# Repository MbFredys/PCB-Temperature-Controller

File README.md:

# Temperature Controller — Hardware Design

Temperature-control PCB design integrating sensing, local displays, setpoint buttons and a relay output.

> **Status: hardware design requiring review and prototype validation.** KiCad sources, a PDF schematic, PCB renders and fabrication exports are published. Firmware is not provided. Temperature accuracy, control stability, Bluetooth operation and electrical safety are not demonstrated by the repository.

## Intended architecture

The published component netlist includes:

- **ATmega328P-AU** microcontroller.
- **MAX31855TASA** thermocouple interface.
- **AD623** instrumentation amplifier in the PT100-related circuit.
- **BTM112** Bluetooth module.
- Two **CA56-12EWA** display assemblies with shift-register/multiplexing circuitry.
- **FINDER 36.11** relay and transistor driver.
- **RAC01-05SGB** AC/DC module and **LM1117-3.3** regulator.

PT100 and thermocouple inputs are design intentions. Supported sensor ranges, excitation, calibration, error budget and fault detection must be established from a complete circuit review and measurements.

## Engineering scope

The project brings together analog sensing, digital display interfacing, a user interface, communication hardware and load control. The available files document the proposed circuit and PCB, rather than a validated controller.

## Required verification

- Confirm module variants, pin assignments, voltage levels and the complete power budget.
- Review the PT100 excitation and amplifier gain, offset, input range and error budget.
- Check thermocouple type, cold-junction behavior and fault response.
- Verify display drive currents and multiplexing timing.
- Define sensor-fault handling, relay safe state, hysteresis/control law and watchdog behavior.
- Review mains separation, creepage/clearance, fusing, enclosure and relay/load ratings before any powered work.
- Develop firmware and record prototype tests.

The AC input range of a selected module does not establish the safety or certification of the complete PCB. Existing Gerbers must not be treated as a fabrication release.

## Files

- [KiCAD files](KiCAD%20files/): editable sources and exported component/net information.
- [PDF schematic](PDF%20Schematic/Controlador-temperatura.pdf).
- [Manufacturing](Manufacturing/): historical fabrication outputs.
- [Release](Release/): PCB renders.
- [Firmware](Firmware/): availability note.

The legacy project uses the `.sch` / `.pro` file format. Preserve an original copy and verify any migration in a supported KiCad version.

## Contributing

Proposed improvements should state the circuit change, its rationale and the checks performed. Keep schematic, PCB, BOM and fabrication outputs synchronized.

## License

CERN-OHL-W-2.0. See [LICENSE](LICENSE) and [COPYING](COPYING).

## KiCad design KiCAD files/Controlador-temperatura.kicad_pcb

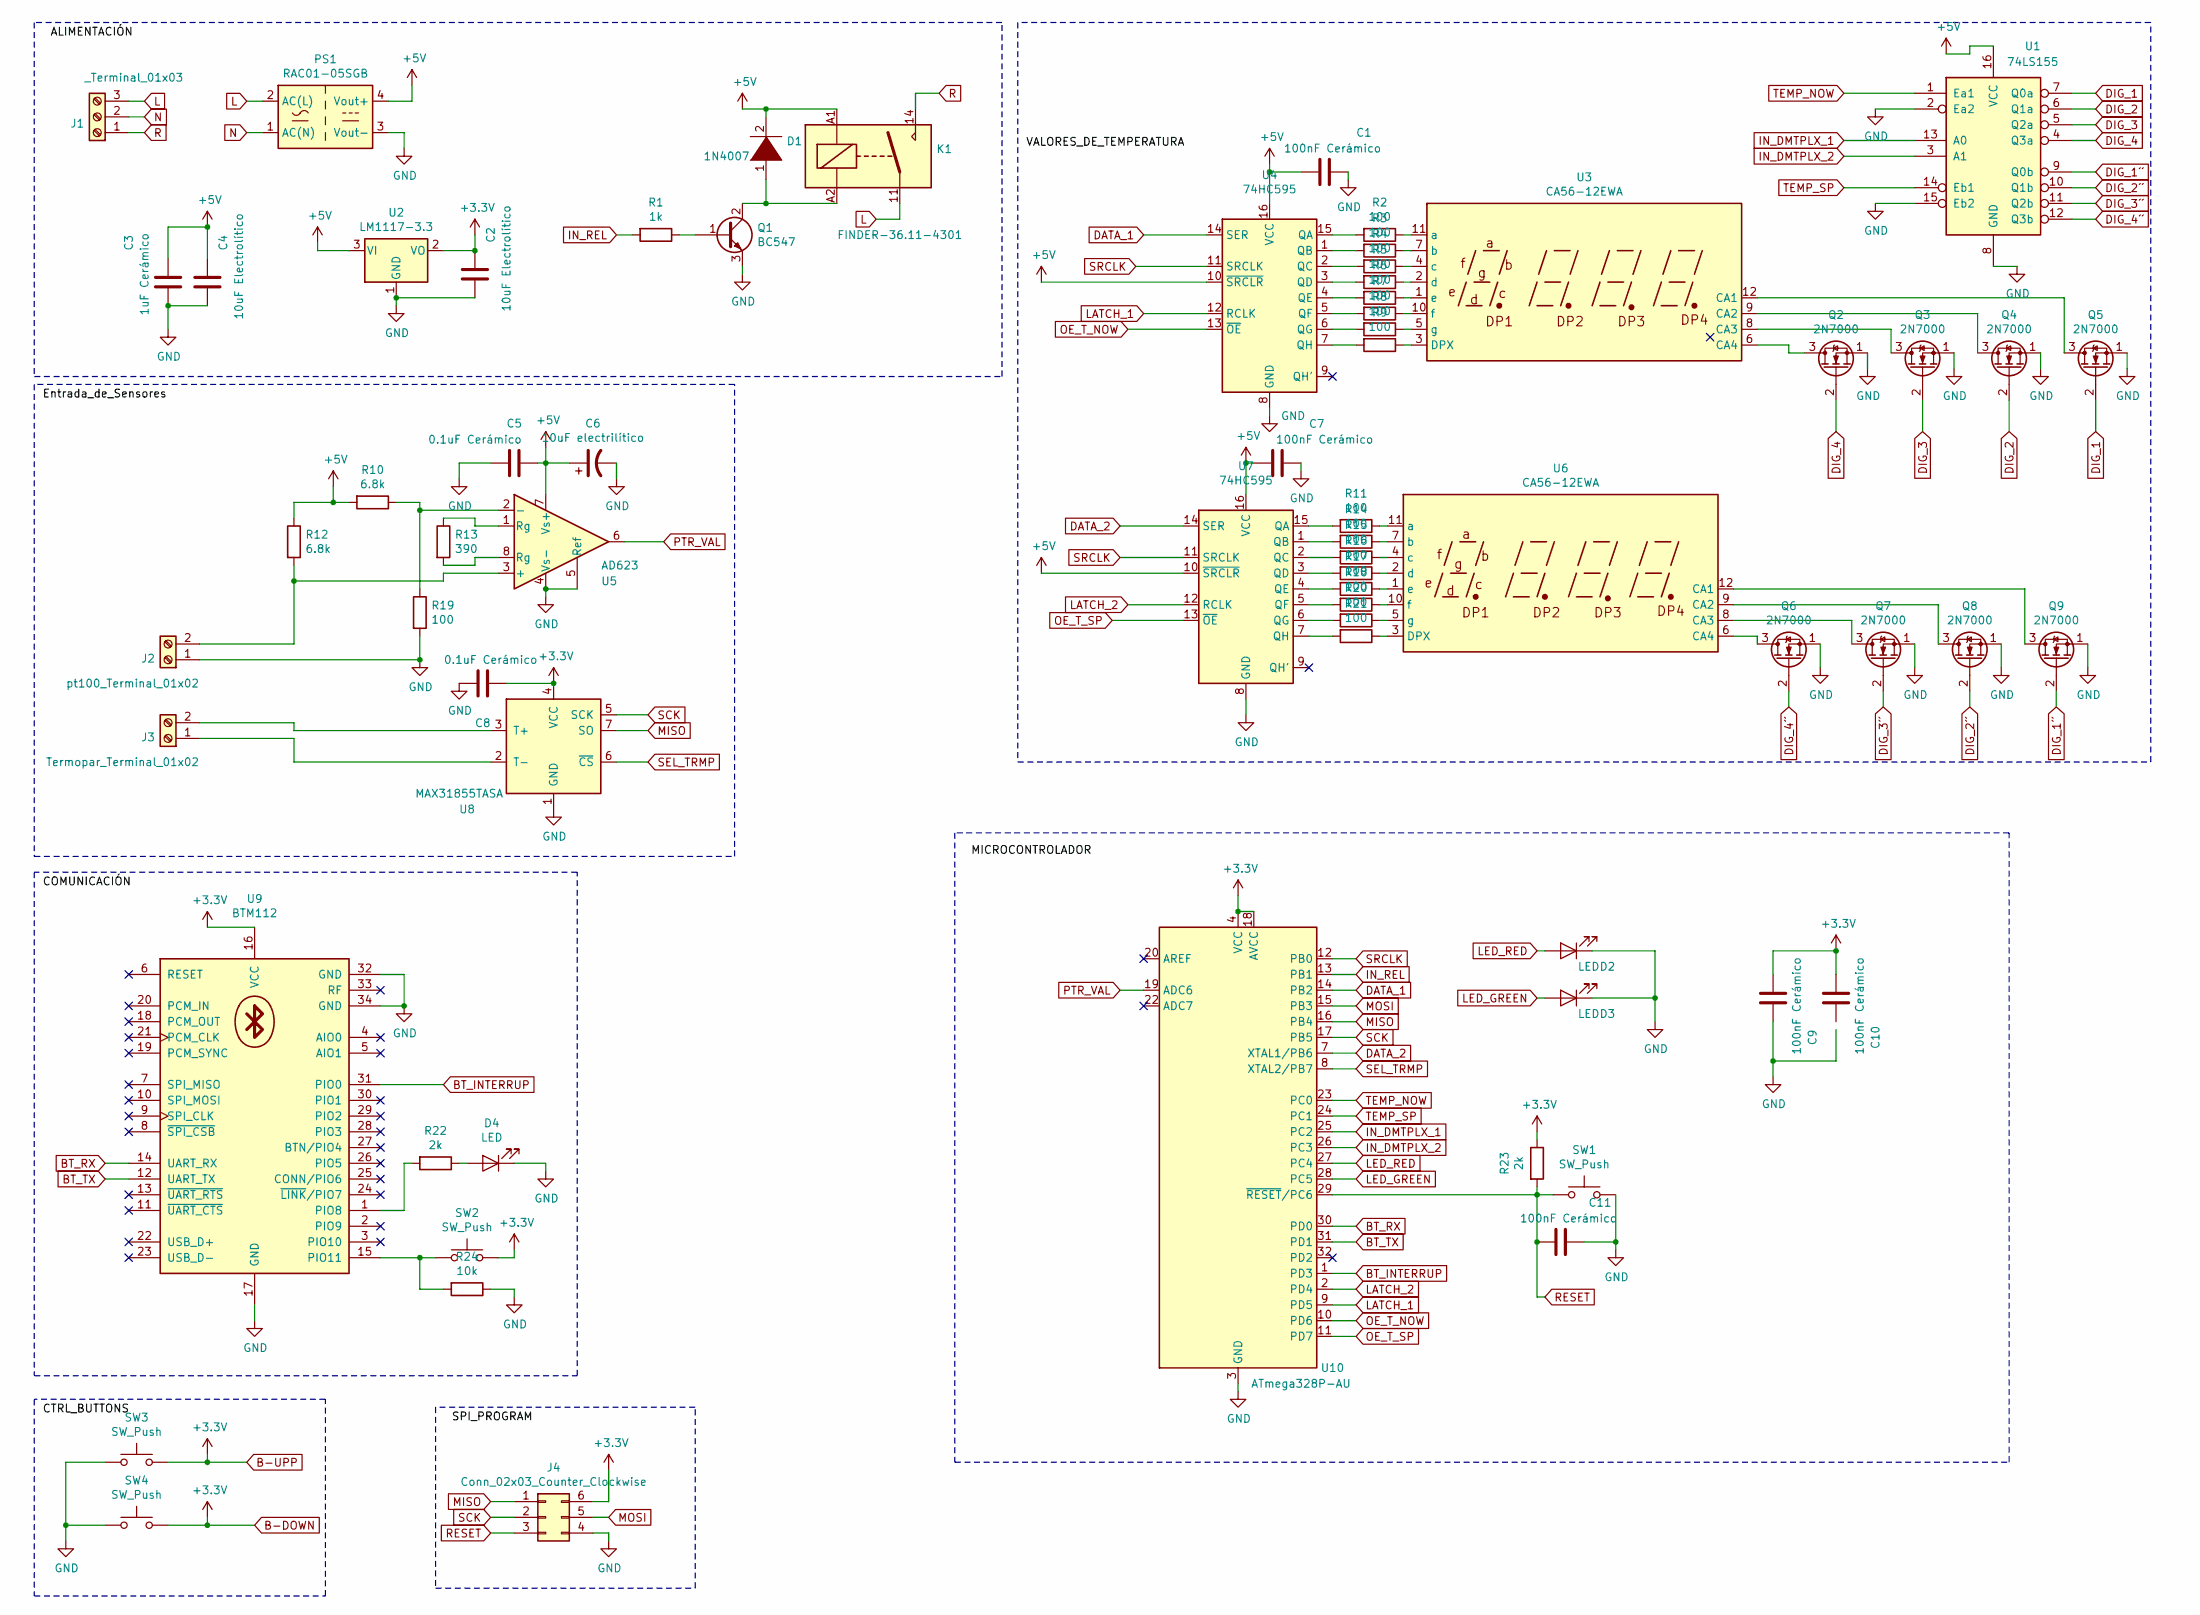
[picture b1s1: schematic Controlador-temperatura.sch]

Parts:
C1, C7, C9, C10, C11: 100nF Cerámico; C_1812_4532Metric_Pad1.30x3.40mm_HandSolder
C2, C4: 10uF Electrolítico; CP_Elec_4x4.5
C3: 1uF Cerámico; C_2512_6332Metric_Pad1.52x3.35mm_HandSolder
C5: 0.1uF Cerámico; C_2512_6332Metric_Pad1.52x3.35mm_HandSolder
C6: 10uF electrilítico; CP_Elec_4x4.5
C8: 0.1uF Cerámico; CP_Elec_4x4.5
D1: 1N4007; D_SOD-323
D2: LED; LED_D3.0mm_IRBlack
D3: LED; LED_D3.0mm_IRGrey
D4: LED; LED_1206_3216Metric
J1: _Terminal_01x03; TerminalBlock_Altech_AK300-3_P5.00mm
J2: pt100_Terminal_01x02; Altech_AK300_1x02_P5.00mm_45-Degree
J3: Termopar_Terminal_01x02; Altech_AK300_1x02_P5.00mm_45-Degree
J4: Conn_02x03_Counter_Clockwise; PinHeader_2x03_P1.27mm_Vertical
K1: FINDER-36.11-4301; Relay_SPST_Finder_32.21-x300
PS1: RAC01-05SGB; Converter_ACDC_RECOM_RAC01-xxSGB_THT
Q1: BC547; SC-59
Q2, Q3, Q4, Q5, Q6, Q7, Q8, Q9: 2N7000; SC-59
R1: 1k; R_0805_2012Metric_Pad1.15x1.40mm_HandSolder
R2, R3, R4, R5, R6, R7, R8, R9, R11, R14, R15, R16, R17, R18, R19, R20, R21: 100; R_0603_1608Metric
R10, R12: 6.8k; R_0805_2012Metric_Pad1.15x1.40mm_HandSolder
R13: 390; R_0603_1608Metric
R22, R23: 2k; R_0805_2012Metric_Pad1.15x1.40mm_HandSolder
R24: 10k; R_0805_2012Metric_Pad1.15x1.40mm_HandSolder
SW1, SW2, SW3, SW4: SW_Push; SW_SPST_B3U-1000P
U1: 74LS155; SOIC-16_3.9x9.9mm_P1.27mm
U2: LM1117-3.3; SOT-223-3_TabPin2
U3, U6: CA56-12EWA
U4, U7: 74HC595; SOIC-16_3.9x9.9mm_P1.27mm
U5: AD623; PowerIntegrations_SO-8
U8: MAX31855TASA; SOIC-8_3.9x4.9mm_P1.27mm
U9: BTM112; BTM-112
U10: ATmega328P-AU; TQFP-32_7x7mm_P0.8mm

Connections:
+5V: C1.1, C3.2, C4.2, C5.1, C6.1, C7.1, D1.2 (A), K1.A1, PS1.4 (Vout+), R10.2, R12.1, U1.16 (VCC), U2.3 (VI), U4.10 (~SRCLR), U4.16 (VCC), U5.7 (Vs+), U7.10 (~SRCLR), U7.16 (VCC)
B-DOWN: C2.2, C8.2, C9.1, C10.1, J4.6, R23.1, SW2.2, SW3.2, SW4.2, U2.2 (VO), U8.4 (VCC), U9.16 (VCC), U10.4 (VCC), U10.6 (VCC), U10.18 (AVCC)
BT_INTERRUP: U9.31 (PIO0), U10.1 (PD3)
BT_RX: U9.14 (UART_RX), U10.30 (PD0)
BT_TX: U9.12 (UART_TX), U10.31 (PD1)
DATA_1: U4.14 (SER), U10.14 (PB2)
DATA_2: U7.14 (SER), U10.7 (XTAL1/PB6)
DIG_1: Q5.2 (G), U1.7 (Q0a)
DIG_1´´: Q9.2 (G), U1.9 (Q0b)
DIG_2: Q4.2 (G), U1.6 (Q1a)
DIG_2´´: Q8.2 (G), U1.10 (Q1b)
DIG_3: Q3.2 (G), U1.5 (Q2a)
DIG_3´´: Q7.2 (G), U1.11 (Q2b)
DIG_4: Q2.2 (G), U1.4 (Q3a)
DIG_4´´: Q6.2 (G), U1.12 (Q3b)
GND: C1.2, C2.1, C3.1, C4.1, C5.2, C6.2, C7.2, C8.1, C9.2, C11.2, D2.1 (K), D3.1 (K), D4.1 (K), J2.1, J4.4, PS1.3 (Vout-), Q1.3 (E), Q2.1 (S), Q3.1 (S), Q4.1 (S), Q5.1 (S), Q6.1 (S), Q7.1 (S), Q8.1 (S), Q9.1 (S), R19.2, R24.1, SW1.2, SW3.1, SW4.1, U1.2 (Ea2), U1.8 (GND), U1.15 (Eb2), U2.1 (GND), U4.8 (GND), U5.4 (Vs-), U5.5 (Ref), U7.8 (GND), U8.1 (GND), U9.17 (GND), U9.32 (GND), U9.34 (GND), U10.3 (GND), U10.5 (GND), U10.21 (GND)
IN_DMTPLX_1: U1.13 (A0), U10.25 (PC2)
IN_DMTPLX_2: U1.3 (A1), U10.26 (PC3)
IN_REL: R1.2, U10.13 (PB1)
L: J1.3, K1.11, PS1.2 (AC(L))
LATCH_1: U4.12 (RCLK), U10.9 (PD5)
LATCH_2: U7.12 (RCLK), U10.2 (PD4)
LED_GREEN: D3.2 (A), U10.28 (PC5)
LED_RED: D2.2 (A), U10.27 (PC4)
MISO: J4.1, U8.7 (SO), U10.16 (PB4)
MOSI: J4.5, U10.15 (PB3)
N: J1.2, PS1.1 (AC(N))
unnamed: D1.1 (K), K1.A2, Q1.2 (C)
unnamed: D4.2 (A), R22.1
unnamed: J2.2, R12.2, U5.3 (+)
unnamed: J3.1, U8.2 (T-)
unnamed: J3.2, U8.3 (T+)
unnamed: Q1.1 (B), R1.1
unnamed: Q2.3 (D), U3.6 (CA4)
unnamed: Q3.3 (D), U3.8 (CA3)
unnamed: Q4.3 (D), U3.9 (CA2)
unnamed: Q5.3 (D), U3.12 (CA1)
unnamed: Q6.3 (D), U6.6 (CA4)
unnamed: Q7.3 (D), U6.8 (CA3)
unnamed: Q8.3 (D), U6.9 (CA2)
unnamed: Q9.3 (D), U6.12 (CA1)
unnamed: R2.1, U3.11 (a)
unnamed: R2.2, U4.15 (QA)
unnamed: R3.1, U3.7 (b)
unnamed: R3.2, U4.1 (QB)
unnamed: R4.1, U3.4 (c)
unnamed: R4.2, U4.2 (QC)
unnamed: R5.1, U3.2 (d)
unnamed: R5.2, U4.3 (QD)
unnamed: R6.1, U3.1 (e)
unnamed: R6.2, U4.4 (QE)
unnamed: R7.1, U3.10 (f)
unnamed: R7.2, U4.5 (QF)
unnamed: R8.1, U3.5 (g)
unnamed: R8.2, U4.6 (QG)
unnamed: R9.1, U3.3 (DPX)
unnamed: R9.2, U4.7 (QH)
unnamed: R10.1, R19.1, U5.2 (-)
unnamed: R11.1, U6.11 (a)
unnamed: R11.2, U7.15 (QA)
unnamed: R13.1, U5.1 (Rg)
unnamed: R13.2, U5.8 (Rg)
unnamed: R14.1, U6.7 (b)
unnamed: R14.2, U7.1 (QB)
unnamed: R15.1, U6.4 (c)
unnamed: R15.2, U7.2 (QC)
unnamed: R16.1, U6.2 (d)
unnamed: R16.2, U7.3 (QD)
unnamed: R17.1, U6.1 (e)
unnamed: R17.2, U7.4 (QE)
unnamed: R18.1, U6.10 (f)
unnamed: R18.2, U7.5 (QF)
unnamed: R20.1, U6.5 (g)
unnamed: R20.2, U7.6 (QG)
unnamed: R21.1, U6.3 (DPX)
unnamed: R21.2, U7.7 (QH)
unnamed: R22.2, U9.1 (PIO8)
unnamed: R24.2, SW2.1, U9.15 (PIO11)
OE_T_NOW: U4.13 (~OE), U10.10 (PD6)
OE_T_SP: U7.13 (~OE), U10.11 (PD7)
PTR_VAL: U5.6, U10.19 (ADC6)
R: J1.1, K1.14
RESET: C11.1, J4.3, R23.2, SW1.1, U10.29 (~RESET~/PC6)
SCK: J4.2, U8.5 (SCK), U10.17 (PB5)
SEL_TRMP: U8.6 (~CS~), U10.8 (XTAL2/PB7)
SRCLK: U4.11 (SRCLK), U7.11 (SRCLK), U10.12 (PB0)
TEMP_NOW: U1.1 (Ea1), U10.23 (PC0)
TEMP_SP: U1.14 (Eb1), U10.24 (PC1)

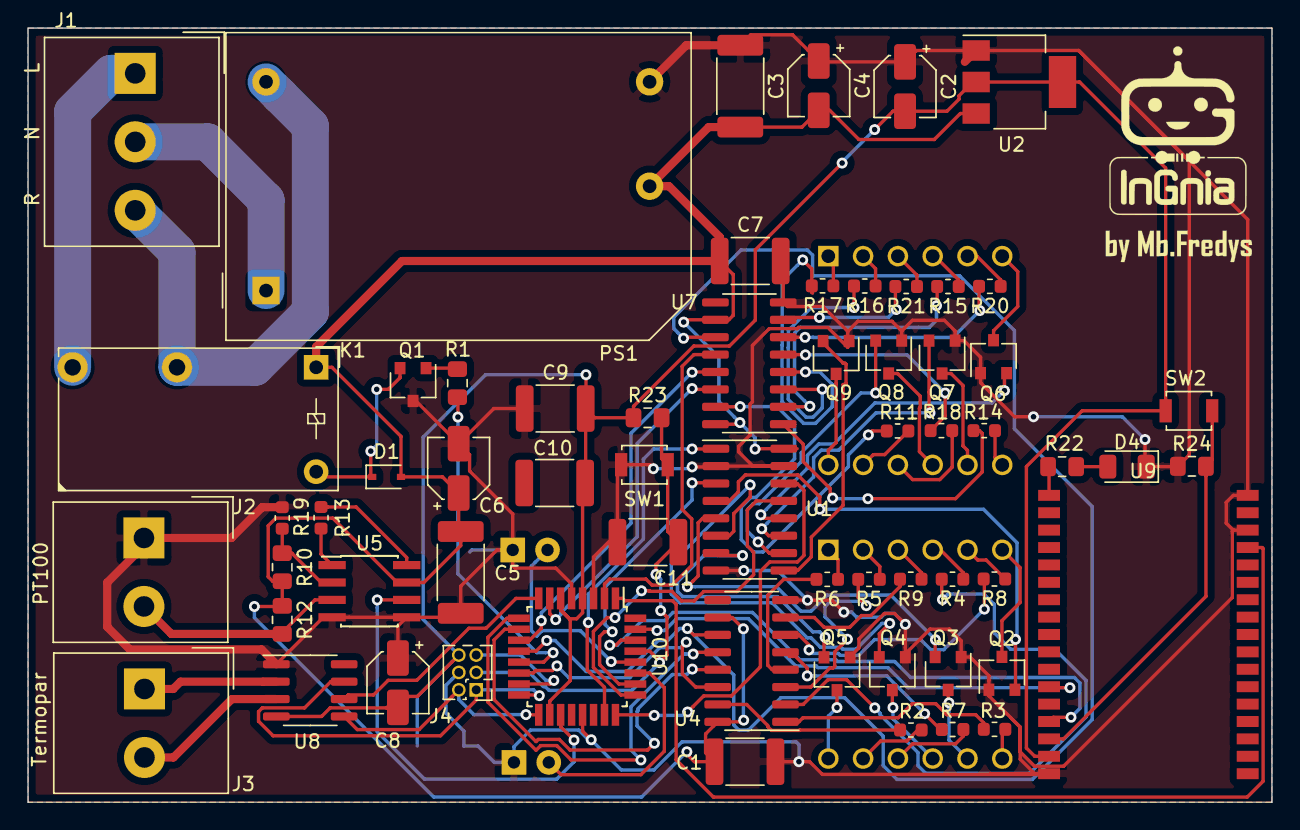
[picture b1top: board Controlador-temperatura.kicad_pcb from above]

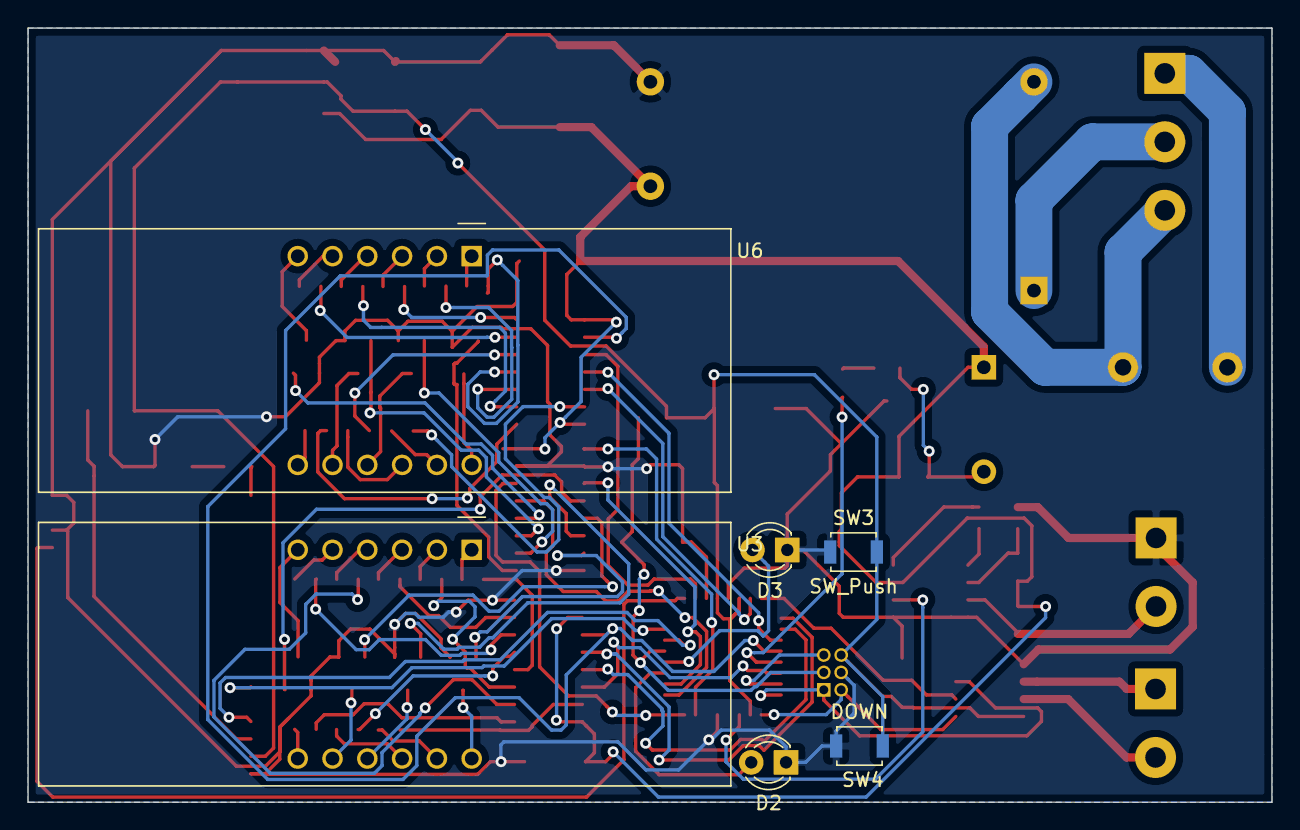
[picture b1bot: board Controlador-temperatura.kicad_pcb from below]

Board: 2 copper layers, 90.8 x 56.5 mm, 68 parts (6 on the bottom side), 88 nets.

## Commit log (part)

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2023-07-16 Agregando archivos al repositorio
2025-12-01 Change license from MIT to CERN OHL v2
2025-12-01 Add CERN Open Hardware Licence Version 2
    Added the CERN Open Hardware Licence Version 2 - Weakly Reciprocal to the project.
2025-12-01 Change license to CERN-OHL-W-2.0 and add badge
    Updated license information and added a license badge.
2025-12-01 Update license link to use HTML anchor tag
2025-12-01 Make license badge in README clickable
    Updated license badge to be a clickable link.
2025-12-01 Update LICENSE
